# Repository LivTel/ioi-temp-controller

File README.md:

ioi-temp-controller
=============

# Overview

This package contains the electronic schematics and arduino code to drive a 
10 microamp excitation current required by the DT-400 series temperature 
sensor diodes inside IO:I's cryostat. This facility was originally provided 
by the Lakeshore 331 temperature controller. 

# Commands

The mac, ip, gateway and subnet addresses need to be configured first.

On upload to an ethernet arduino, a socket server is instantiated to serve a limited command set previously 
used by IO:I's ICS. The four commands that are currently available are:

| Command        | Description                        |
| :------------- | :----------------                  | 
| KRDG?A         | Read temperature from sensor A (K) |
| KRDG?B         | Read temperature from sensor B (K) |
| VRDG?A         | Read voltage from sensor A (V)     |
| VRDG?B         | Read voltage from sensor B (V)     |

The socket server is blocking, and must not be held open for prolonged periods by a single machine.

## Schematic

The schematic is as follows.

The LM134 IC provides a temperature dependent current source. The magnitude of this 
current source is modulated by the two digital pots R1 & R2 (MCP41100). The 
temperature dependence is largely removed by diode D1 (1N4933). 

Note that the ETHCS pin is not used for clock selects!

# I/O Configuration

Definitions for I/O should not need to be changed if the wiring follows the schematic above *and* the 
temperature sensor wiring follows:

| Pin            | Description       |
| :------------- | :---------------- | 
| 2              | T2 V-             |
| 3              | T2 V+             |
| 4              | T1 V-             |
| 5              | T1 V+             |

# Current Magnitude and Temperature Calibration Coefficients

The set current [**SET\_CURRENT**] must be set so that it lies within the capability defined by the relative 
resistances of the digital pots. See p8 of the LM234 component manual in `man/` for a description of how the 
current magnitude is defined using the two pots.

The temperature sensor calibration is defined by the coefficients [**DIODE\_TEMPERATURE\_COEFFS**] and 
a corresponding reference voltage [**REFERENCE\_VOLTAGE**]. This has been set (as of 19/10/15) for 
a DT471 series diode.

# Known Issues

A 2.5V reference voltage is fed to the reference pin to increase the accuracy of the A2D conversion whilst still
remaining in range of the full output voltage of the diode at RT down to 80K. Currently, with the 10bit conversion 
and a diode temperature coefficient of -2.5mV/degC, the system is only accurate to [2.5/(2^10)]/(2.5*10^-3) 
degC == 1 degC. This could be improved by either i) addition of a more accurate A2D circuit, or ii) reducing the range 
over which the sensor can be read.

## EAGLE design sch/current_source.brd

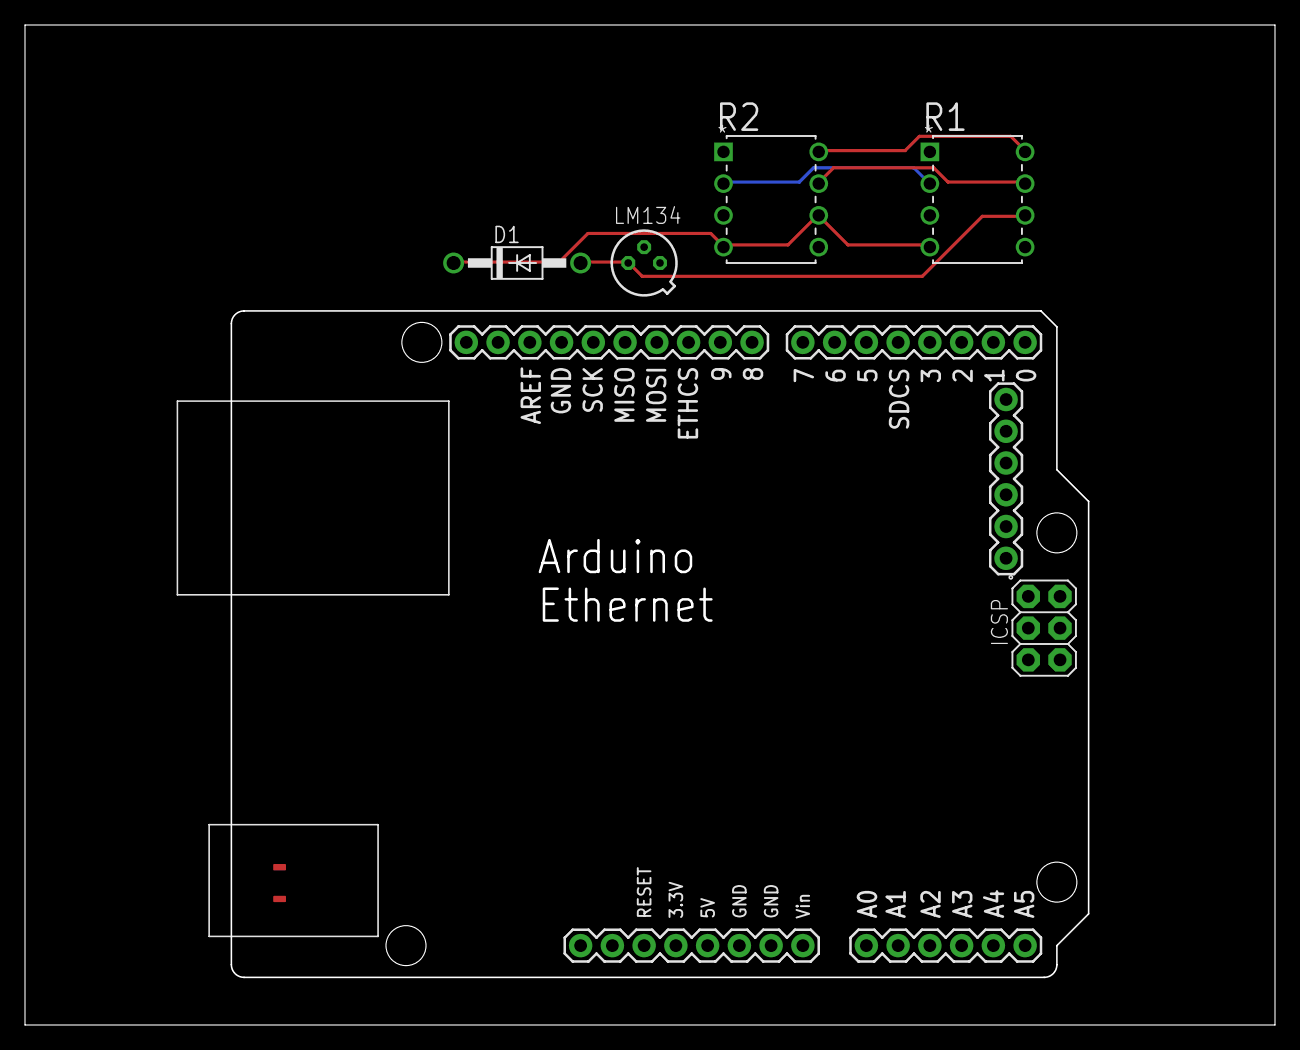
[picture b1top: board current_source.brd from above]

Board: 2 copper layers, 100.0 x 80.0 mm, 5 parts (0 on the bottom side), 9 nets.

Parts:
D1: 1N4933; DO41-10
LM134: TO46
PCB1: ARDUINO_ETHERNET
R1, R2: MCP41100; DIP254P762X533-8

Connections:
I_OUT: D1.C, PCB1.GND., R1.4, R2.4, R2.6
unnamed: LM134.1, R1.7, R2.7
unnamed: D1.A, LM134.3, R1.6
unnamed: LM134.2, PCB1.5V
unnamed: PCB1.ETHCS, R2.1
unnamed: PCB1.9, R1.1
unnamed: PCB1.SCK, R1.2, R2.2
unnamed: PCB1.MOSI, R1.3, R2.3
VDD: R1.8, R2.8

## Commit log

2015-10-12 init commit
2015-10-26 Added differential reading.
2016-03-31 Updated README and images.
2016-03-31 Removed duff image.
